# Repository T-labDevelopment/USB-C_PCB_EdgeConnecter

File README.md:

# USB-C PCBエッジ検証基板 Rev.0.7 — Windows短パス配布版

## 最新の修正（2026-11-13）
- **B.Cu接点24個から短い0.20mmの銅箔引出し配線を追加済み。** B1GND・B12GNDを含む。
- **LED帰路の`BAT_NEG`専用B.Cuベタを追加。** USB-CのGND検査端子には直接接続しない。
- GND検査は8経路（16接点）で、既存の対応する抵抗・LEDを維持。
- KiCadで銅箔ゾーンを再フィル（Bキー）してからDRCを実施する必要があります。**追加したゾーンの充填とERC/DRCは未検証です。**
- **未完成**：B.Cuの24本は引出し部分のみで、その他の全信号経路とBAT_POS給電配線は未配線です。製造承認済みではありません。

変更詳細：[GND・B.Cu接点引出し監査](REV07_BCU_GND_ESCAPE_FIX_2026-11-13.md)／[GND対応表](gnd_sense_map_rev07.csv)。

## Windows ZIP展開エラーへの対処

この`pkg-r07`は現行KiCadソースを最上位フォルダに格納し、不要な旧CH25電池ホルダーフットプリントと過去のZIPを除外した短パス配布専用ブランチです。

1. [pkg-r07 ZIP](https://github.com/T-labDevelopment/USB-C_PCB_EdgeConnecter/archive/refs/heads/pkg-r07.zip)をダウンロード。
2. `C:\PCB\`など短い場所に展開する。
3. 展開フォルダ直下の`USB_C_Loop_Tester.kicad_pro`をKiCad 10.x安定版で開く。
4. `USB_C_PCB_Edge.pretty/`・`USB_C_PCB_Edge.kicad_sym`・`fp-lib-table`・`sym-lib-table`はファイル階層を維持する。参照は`${KIPRJMOD}`相対パスです。

## 電気・機構構成

- J1/J2は14P USB2形状、J3/J4は実験用10P USB-Cエッジ接点形状。
- D1～D24の24個のLEDとR1～R24の22kΩ抵抗による個別接点導通表示。
- USB-Cの接点48パッドを基板内側へ2.4mm延長した形状を維持し、**その内側からB.Cu銅箔配線をさらに引出し**。
- ラッチKeepoutは16箇所、電池帰路B.Cuゾーンは1箇所。
- 電源は外付けCR2032×1、基板にはKiCad標準の2線はんだ付けパッド。
- 公称板厚0.8mm・2層・ENIG検討中。

**USB-CのGND接点を電池マイナスの銅箔面へ直接つなぐとLED検査を迂回するので禁止です。** ケーブルプラグ内部でGND・VBUSが共通化されるため、各LEDは接点1本ごとの良否を保証できません。

**残る必須事項**：すべての配線完成、KiCad 10 ERC/DRC、基板エッジ製造公差・マスク・機械嵌合・LED光量の実機確認。

Git管理の本開発作業ブランチ：`fix/usb-c-rev07-bcu-gnd-escape`。旧開発履歴は元リポジトリに維持し、`main`へは未統合。

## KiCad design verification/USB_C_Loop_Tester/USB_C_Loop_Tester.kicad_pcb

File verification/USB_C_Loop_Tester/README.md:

# USB-C 14P・10P 個別接点LED検証基板（Rev.0.7）

## 2026-11-13 B.Cu配線開始・GNDの帰路整理（最新作業版）

- J1～J4の下側接点全24個に、幅0.20mm・局所X=-0.20→+2.54mmの**同一ネットへの短いB.Cu配線**を配置しました。B1GND/B12GNDも含みます。
- USB-CのGND接点は導通試験用の独立ネットのまま残し、電池マイナスへ直結しません。
- LED24個のカソードと電池マイナスをつなぐ**BAT_NEG専用のB.Cuベタ（銅箔ゾーン）**を追加しました。USB側GND接点のネットとは別です。
- KiCadの **B（ゾーン再フィル）→DRC** で実際のクリアランス・給電帰路を必ず確認してください。B.Cu24本は接点からの引出し部分のみで、その他の信号とBAT_POSは未配線です。
- [GND8経路の対応表](gnd_sense_map_rev07.csv)／[GND・B.Cu変更監査](REV07_BCU_GND_ESCAPE_FIX_2026-11-13.md)。

**これまでの「PCBトラック0本」という説明は旧版の履歴です。最新作業版はトラック24本・銅箔ゾーン計17件です。ERC/DRC未実施・未完成のため製造承認不可。**

---

> **Windows ZIP展開エラー0x80010135への対応**：GitHubの長いブランチZIPではなく、現行KiCadファイルだけをルート階層に置いた短パス配布ブランチ [pkg-r07](https://github.com/T-labDevelopment/USB-C_PCB_EdgeConnecter/archive/refs/heads/pkg-r07.zip) を使用してください。旧CH25電池ホルダー用フットプリントは現行回路で未使用のため除外済みです。ダウンロード後は `C:\PCB\` など短い場所へ展開してください。元の開発データと履歴はこのブランチに保存しています。

## 2026-11-13 接点延長の反映（現行作業版）

画像で示された外側GND接点の引出し配線を短くするため、J1～J4の**全48銅パッドを基板内側へ2.4mm延長**しました。フットプリント内の外側嵌合端は維持し、内側端のみ `X=-2.385mm → +0.015mm` へ変更しています。配線開始位置はKeepout境界（X=-0.635mm）より基板内側へ0.65mm進みます。

- 14P/10PライブラリとPCB埋め込みの4コネクタ、`pad_positions.csv`を更新。
- 接点幅0.25mm、隣接銅間隔0.25mm、ラッチKeepout、端子ごとの独立ネットとLED・抵抗は維持。
- 露出銅箔とレジスト開口も延長するため、嵌合・半田レジスト・ENIGは未実機確認。
- **PCB配線は未実施**。KiCad 10のERC/DRC・製造検証は未実施。

詳細：[接点延長と静的検査](REV07_INBOARD_PAD_EXTENSION_2026-11-13.md)。

---

## 現行Rev.0.7 — 全24接点に独立した抵抗とLED

14PのJ1/J2に14系統（R1～R14、D1～D14）、10PのJ3/J4に10系統（R15～R24、D15～D24）を設けました。各USB-C銅接点はすべて別ネットで、グローバルラベルを介して専用抵抗・LEDへ接続します。

- 基板側の電源ネットのみBAT_POS/BAT_NEGを共用し、24個の抵抗入力／24個のLED帰路をまとめます。USB接点を基板上で短絡・グループ化しません。
- 電池は外付けCR2032×1、BT1は標準2線はんだ付けパッド。パッド1＋＝(31.0,18.0)mm、パッド2−＝(35.2,18.0)mm。
- **PCB：53フットプリント／146パッド／50ネット、銅箔配線0本。回路図：53部品・24分岐。**
- 0.8mm・2層・ENIG、USB-C接点形状とラッチKeepoutは旧版から維持。
- [全24回路の配線対応](channel_map_rev07.csv)／[回路と制約の説明](REV07_INDIVIDUAL_CONTACT_CIRCUIT.md)／[部品表](bom.csv)。

**重要：** USB-CのVBUS/GNDは通常ケーブル内部で共通化され、USB2.0ケーブルのB6/B7やCCは通常の1対1導通を前提にできません。すべてのLEDの点灯が正常なわけではなく、各接点1個だけの接触不良を保証して検出することもできません。

**未完了：** KiCad 10でのERC・DRC、PCB配線、Gerber、製造メーカーの加工承認、実機導通とLED光量試験。製造可能とは判定していません。

---

## 以下はRev.0.6以前の履歴であり、現行の回路仕様ではありません。

# USB-C 14P・10P 統合信号別LED導通検証基板（Rev.0.6）

## Rev.0.6 電源部の仕様変更：外付けCR2032／標準2線パッド

**採用仕様：基板直付けCH25-2032LFを廃止し、外部のCR2032ホルダーから絶縁リード線2本で給電する方式。**

以前のCH25-2032LF専用フットプリントは登録・極性確認・機構寸法の制約が多いため、現行PCBのBT1にはKiCad公式の標準フットプリント `Connector_Wire:SolderWire-0.25sqmm_1x02_P4.2mm_D0.65mm_OD1.7mm` を設定しました。独自の電池ホルダー用フットプリントを導入せずにKiCad 10の標準ライブラリで編集可能です。

- BT1パッド1（＋／BAT_POS）：基板座標(76.0, 90.0)mm、BT1パッド2（−／BAT_NEG）：(80.2, 90.0)mm。
- 2端子ピッチ4.2mm、ドリルφ0.85mm、ランドφ1.85mm。約0.25mm²の被覆付きリードを想定。
- CH25-2032LF（秋月電子100706）は**外付けでリード線を取り付ける場合の候補**として保持します。主基板へ直接実装しません。既に購入している場合も利用できますが、THT端子を配線用に使う加工・固定は実装時に確認してください。
- 電源はCR2032×1、スイッチなし。14P・10P各2端子／6個の信号別LEDは一切変更しません。
- 電池を入れない状態で極性と短絡を点検し、配線の引張り荷重がはんだ付け部分に掛からないよう固定・絶縁してください。
- **PCB銅箔配線は依然0本、KiCad 10のERC/DRCと実物検証は未実施です。**

詳しくは [新しいBT1外付け給電仕様](docs/BT1_EXTERNAL_CR2032.md) を参照してください。

## 旧検討案：BT1 CH25-2032LF基板直付け（Rev.0.5時点、現在は非採用）

> この節から下の旧Rev.0.5設計履歴は現在の採用仕様ではありません。Rev.0.6では外付けCR2032＋標準2線パッドが正式な接続方式です。

秋月電子 [販売コード100706](https://akizukidenshi.com/catalog/g/g100706/) のCR2032基板取付ホルダー `CH25-2032LF` に変更しました。旧Keystone用フットプリントは使用しません。新規`USB_C_Test_Parts.pretty`内の正規寸法図ベースの専用フットプリントに変更し、PCB側に電気端子用穴2個（20.0mmピッチ）、位置決めNPTH穴3個を追加しました。

**極性とPCB表裏方向はまだ実物確認前です。** 現在は下側リードをBAT_POS、上側をBAT_NEGとして仮定しています。設計確定前に電池を抜いた状態で金属クリップと2端子の導通を実測してください。詳細：[BT1 CH25-2032LF実装資料](docs/BT1_CH25-2032LF.md)。

PCBは依然として銅箔配線がありません。KiCad 10によるERC/DRC、実装、機械的嵌合は未検証です。

**以下は旧Rev.0.5時点の設計説明です。** ユーザー提示の左右2端子・中央電池・信号別LEDという概念図に基づき、14Pと10Pを1枚に統合し、ケーブルを挿入するだけで各信号の導通状態がLEDで見えるように再構成しました。

| 項目 | 14P検証（上段） | 10P検証（下段） |
| --- | --- | --- |
| USB-C接点 | J1（送出）、J2（受け） | J3（送出）、J4（受け） |
| VBUS | R1→D1 | R5→D5 |
| CC1/CC2（共用） | R2→D2 | R6→D6 |
| USB D+（A6/B6） | R3→D3 | 非搭載 |
| USB D−（A7/B7） | R4→D4 | 非搭載 |
| GND | J1→ケーブル→J2の共通帰路 | J3→ケーブル→J4の共通帰路 |

電源はBT1のCR2032（公称3V）1個。各LEDには22kΩを直列に接続し、入力スイッチ、制御IC、USB PD回路を置きません。

**実際の導通経路（14PのVBUS例）**

`CR2032＋ → R1 → J1 VBUS → 外部C-Cケーブル → J2 VBUS → D1（A→K） → J2 GND → 外部C-Cケーブル → J1 GND → CR2032−`

10PのVBUS/CC、および14PのCC/D+/D−も同様に、それぞれの抵抗とLEDを通ります。GNDは戻り線です。**J1とJ2、J3とJ4を基板上で直接配線しない**ので、未接続のケーブルは導通扱いになりません。電池の＋と−の不要な交差は避けてあります。

### この版で実施したこと

- 回路図は17部品、**全74端子**、**85本のワイヤー／18か所のジャンクション／16ネット／ネットラベル0**。端子と配線は50mil（1.27mm）グリッドに配置。
- 回路図内の意図しない異ネット接続0、途中で分断されたネット0、配線されていない端子0を静的検査。
- 各LEDの極性を確認。モデル上で「未接続・14Pのみ・10Pのみ・双方・1信号断線・GND断線」計8パターンの期待点灯を確認。
- PCBは既存のUSB-Cエッジ接点・電池ホルダーを維持し、LED D1～D6と抵抗R5/R6の配置を整理。PCB74パッドの番号・ネット割当は変更しません。

**重要：これは電気的な論理構成が成立することの検証です。** KiCad 10でのERC実行・DRC・実機嵌合・LED光量試験を実施したという意味ではありません。PCBの銅箔配線は依然0本で、製造しても動作しません。

詳細は [Rev.0.5統合回路・論理検証資料](REV05_UNIFIED_CIRCUIT.md) を参照してください。旧Rev.0.4以前の記載は以下に履歴として保持します。

---

## 過去の検討・修正履歴

## ERC実測レポートに基づく修正（2026-11-12 / Rev.0.4）

ユーザー提供のKiCad ERCレポート：**20エラー（未接続ピン18、電源入力未駆動2）、19警告（未接続配線端19ではなく18、シンボル不一致1）**。

- 単なる文字ベースの端点一致ではKiCad ERCで多数の未接続が残ったため、電源配線・LED帰路を端子直結の連続線に再配置し直しました。
- 14P/10P各2個の全接点、6灯LED、CR2032、6個の22kΩは維持。ネットラベルは0個、**実配線63本・明示接続点18個**。
- USB-C検証治具ではVBUS/GNDは電源入力ではなく測定用受動接点です。製品用の元シンボルは変更せず、`USB_C_Test_14P_USB2_NoShield` と `USB_C_Test_10P_Power_NoShield` をプロジェクト専用に追加し、各端子のVBUS/GNDを受動型として設定。**PWR_FLAGは設置せず**、電源の存在を偽装しない方針です。
- `Device:Battery_Cell` キャッシュをKiCad 10.x系の正式シンボルデータに更新しました。お使いのローカルKiCadライブラリと同一リビジョンであるかは未確認です。
- **静的監査：74シンボル端子／74PCBパッド、16ネットに一致、未接続端点0件、PCBネットとの相違0件。** 交差のみの2箇所はジャンクションなしで別ネット扱いです。
- **重要：修正版のKiCad 10 ERCはまだ実行していません。エラー・警告が0件になったとは断定できません。** 結果確認には再度KiCadのERCが必要です。
- PCBは配置案のままで、**銅箔配線は0本**（製造不可）。端子形状・基板厚は変更していません。

詳細：[ERC修正監査](ERC_REPAIR_AUDIT_2026-11-12.md)。

## Rev.0.3（2026-11-12）回路図の実配線化・部品再配置

- 回路図のネットラベルを**全廃（0個）**し、94本のワイヤーと18個の接続点で全信号を直接接続しました。配線・接続点は50milグリッドに整列しています。
- J1/J2（14P）は回路図上段、J3/J4（10P）は下段。送出側へR1～R6、受け側へD1～D6を配置し、CR2032の共通給電と、ケーブル経由のGND帰路を明示しました。
- PCBではUSB-Cエッジ端子と電池ホルダーの位置を固定し、抵抗6個・LED6個を検査系統ごとに再配置。パッド座標一覧も更新しました。
- 静的な接続グラフ検査：**74端子／16ネット、未接続端子0、異ネット短絡0**。基板上の配線は**0本**で未完成です。
- 回路図をKiCad 10で実際に開いて確認する工程、ERC/DRC、製造可否とLED点灯試験は**未実施**です。

**採用案：ケーブルを挿すだけで該当するLEDが点灯。スイッチは設けません。**

- 1枚の基板に14Pエッジ端子×2（J1/J2）、10Pエッジ端子×2（J3/J4）。
- CR2032×1、3mm高輝度・低電流赤色LED×6、22kΩ×6（いずれも手はんだしやすいTHT）。
- 14P/10Pそれぞれにe-marker非搭載・無通電の受動型USB-C⇔USB-Cケーブルを接続して判定。
- FR-4、2層、板厚0.8mm、接点ENIG、暫定突出長6.2mm。USB接点部分にシルクなし。

## KiCad 10での開き方

1. 現行Rev.0.6はGitHubの `feature/usb-c-external-cr2032-wire-pads` ブランチから取得します。`verification/USB_C_Loop_Tester/` 以下のファイルとライブラリをフォルダーごと保持してください。`verification/releases/` にある旧版ZIPはRev.0.6以前の履歴データです。
2. `verification/USB_C_Loop_Tester/USB_C_Loop_Tester.kicad_pro` をダブルクリックするか、KiCad 10の「ファイル → プロジェクトを開く」から選択します。
3. 左のプロジェクトツリーで同名の `.kicad_sch`（回路図）と `.kicad_pcb`（基板）を選択します。
4. `USB_C_PCB_Edge.kicad_sym`、`USB_C_PCB_Edge.pretty/`、`sym-lib-table`、`fp-lib-table` はプロジェクトに同梱されています。**フォルダー構成を変更しないでください**。標準のDevice/LED、Device/R、Device/Battery_Cell等のKiCad 10標準ライブラリは本体側が必要です。

**重要**：今回はKiCadが認識するプロジェクト構成とファイル構文を静的検査したものです。この環境ではKiCad 10の実行ファイルがなく、実際のGUI読み込みとERC/DRCには未着手です。またPCBは配線0本で、製造しても動作しません。

## LEDと信号の対応

| 系統 | LED | 確認する信号 | 同一機能として集約するパッド |
|---|---|---|---|
| 14P（J1⇄J2） | D1 | VBUS | A4/A9/B4/B9 |
| 14P（J1⇄J2） | D2 | CC | A5(CC1)/B5(CC2) |
| 14P（J1⇄J2） | D3 | D+ | A6/B6 |
| 14P（J1⇄J2） | D4 | D− | A7/B7 |
| 10P（J3⇄J4） | D5 | VBUS | A4/A9/B4/B9 |
| 10P（J3⇄J4） | D6 | CC | A5(CC1)/B5(CC2) |

GND（A1/A12/B1/B12）は14Pと10Pで独立した**共通の帰路**として使います。基板内で戻り側GND（J2/J4）をBAT_NEGに直結していないため、ケーブルのGND経路が断線した場合は、その系統のLEDがまとめて消灯します。GNDだけの独立LEDは設けません。

**同じ機能の端子はLEDを共用**しますが、14Pと10Pでは検証対象が違うため、同じVBUSやCCであっても系統間でLEDを共用しません。片方のケーブルだけが接続されたときにもう一方の表示が点灯しないようにするためです。

### 回路経路（各LED共通）

`CR2032+ → R1～R6(各22k) → J1/J3側の該当信号 → C-Cケーブル → J2/J4側の該当信号 → D1～D6（アノード→カソード） → 戻り側GND → C-CケーブルのGND → CR2032−`

接続した信号と共通GNDの両方に導通があれば、対応するLEDだけが点灯します。抜けば消灯します。2本同時接続時には最大6灯が点灯します。

## 判定上の制限

- **e-marker付きのパッシブケーブルは検証対象から除外します。** この簡易治具はCC1/CC2を直結しているため、ケーブルのVCONN側Ra（約1kΩ）に影響され、正常なケーブルでもCC LEDが点灯しない可能性があります。e-marker非搭載の一般的なUSB 2.0 C-Cケーブルを基準に評価してください。

- 表裏のA/B端子や複数VBUS・GND端子を並列接続しているため、**同一信号群内の個別パッド1個の断線は判別できない場合があります**。
- CCは一般のC-Cケーブルで1本の有効信号線です。A5/B5の両方をこの**無電源ケーブル検証専用基板**では意図的にまとめています。実製品のUSB-CデバイスではCC1とCC2を直結せず、規格どおりの終端を使用してください。
- LED点灯は簡易導通確認であり、接触抵抗の定量評価、隣接信号短絡の網羅的検出、USB2.0列挙、USB PD、ESP32の書き込み成功を保証しません。
- ケーブルの**両端をそれぞれ反転**して、点灯の変化と接触安定性を確認してください。

## 電源・安全

22kΩで赤色LED順方向電圧を約1.8Vと仮定すると、1灯あたり約0.055mA、6灯で合計約0.33mAです（**計算上の参考値で実測ではありません**）。CR2032の標準連続負荷0.2mAより大きいため、挿入試験は短時間とし、使用後はケーブルを抜いて消灯させてください。低電流でも見える赤色LEDの部品選定・光量は実機確認対象です。

**この基板は外部のUSB機器に接続できません。** CR2032による電圧をUSB端子に出す検証治具です。PC、充電器、モバイルバッテリー、給電中のUSB機器、アクティブケーブル等に接続しないでください。無通電の受動型C-Cケーブルのみを試験対象とします。

## 製造・動作検証状態

- KiCad回路図、PCB内の部品配置とパッドのネット割当、BOMを更新しました。
- PCBは**配線未実施（銅箔配線セグメント0件）**です。このデータをそのまま製造してもLEDは動作しません。
- KiCad 10実環境のERC/DRC、外形の接続、製造データ、嵌合・導通・光量確認は未実施。
- GND接点とEdge.Cutsとの約0.17mmクリアランスについて、基板メーカーの加工承認が必要です。
- 旧来の2灯直列方式は `../USB_C_Loop_Tester_Series/`、スイッチ付き案はGit履歴で参照できます。

## 参考
- USB Type-C規格資料：https://www.usb.org/documents
- Panasonic CR2032（3V、標準負荷0.2mA）：https://energy.panasonic.com/jp/business/products/lithium/coin-cr-standard/models/CR2032
- PCBエッジ方式先行例：https://github.com/AnasMalas/pcb-edge-usb-c

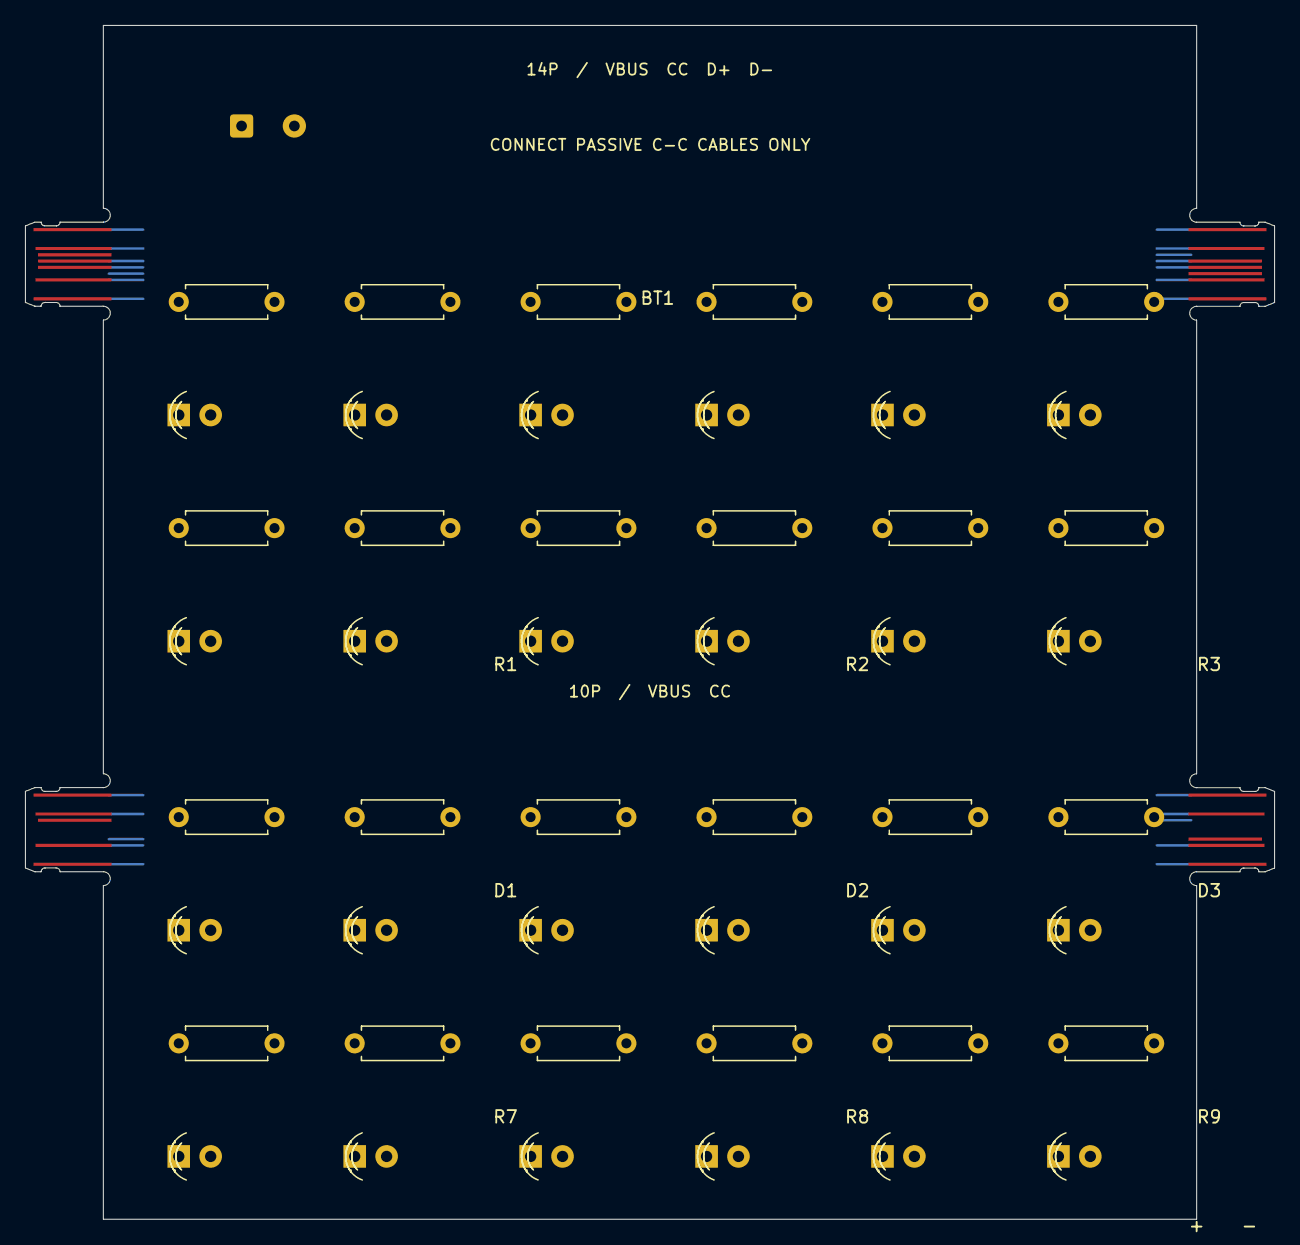
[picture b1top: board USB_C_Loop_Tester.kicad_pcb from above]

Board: 2 copper layers, 99.4 x 95.0 mm, 53 parts (0 on the bottom side), 50 nets.

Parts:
BT1: CR2032_EXTERNAL; SolderWire-0.25sqmm_1x02_P4.2mm_D0.65mm_OD1.7mm
D1, D2, D3, D4, D5, D6, D7, D8, D9, D10, D11, D12, D13, D14, D15, D16, D17, D18, D19, D20, D21, D22, D23, D24: RED; LED_D3.0mm
J1, J2: 14P; USB_C_Edge_14P_USB2_NoSilk
J3, J4: 10P; USB_C_Edge_10P_Power_NoSilk
R1, R2, R3, R4, R5, R6, R7, R8, R9, R10, R11, R12, R13, R14, R15, R16, R17, R18, R19, R20, R21, R22, R23, R24: 22k; R_Axial_DIN0207_L6.3mm_D2.5mm_P7.62mm_Horizontal

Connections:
BAT_NEG: BT1.2, D1.1, D2.1, D3.1, D4.1, D5.1, D6.1, D7.1, D8.1, D9.1, D10.1, D11.1, D12.1, D13.1, D14.1, D15.1, D16.1, D17.1, D18.1, D19.1, D20.1, D21.1, D22.1, D23.1, D24.1
BAT_POS: BT1.1, R1.1, R2.1, R3.1, R4.1, R5.1, R6.1, R7.1, R8.1, R9.1, R10.1, R11.1, R12.1, R13.1, R14.1, R15.1, R16.1, R17.1, R18.1, R19.1, R20.1, R21.1, R22.1, R23.1, R24.1
DST_J2_A1GND: D1.2, J2.A1GND
DST_J2_A4VBUS: D2.2, J2.A4VBUS
DST_J2_A5CC1: D3.2, J2.A5CC1
DST_J2_A6D+: D4.2, J2.A6D+
DST_J2_A7D-: D5.2, J2.A7D-
DST_J2_A9VBUS: D6.2, J2.A9VBUS
DST_J2_A12GND: D7.2, J2.A12GND
DST_J2_B1GND: D8.2, J2.B1GND
DST_J2_B4VBUS: D9.2, J2.B4VBUS
DST_J2_B5CC2: D10.2, J2.B5CC2
DST_J2_B6D+: D11.2, J2.B6D+
DST_J2_B7D-: D12.2, J2.B7D-
DST_J2_B9VBUS: D13.2, J2.B9VBUS
DST_J2_B12GND: D14.2, J2.B12GND
DST_J4_A1GND: D15.2, J4.A1GND
DST_J4_A4VBUS: D16.2, J4.A4VBUS
DST_J4_A5CC1: D17.2, J4.A5CC1
DST_J4_A9VBUS: D18.2, J4.A9VBUS
DST_J4_A12GND: D19.2, J4.A12GND
DST_J4_B1GND: D20.2, J4.B1GND
DST_J4_B4VBUS: D21.2, J4.B4VBUS
DST_J4_B5CC2: D22.2, J4.B5CC2
DST_J4_B9VBUS: D23.2, J4.B9VBUS
DST_J4_B12GND: D24.2, J4.B12GND
SRC_J1_A1GND: J1.A1GND, R1.2
SRC_J1_A4VBUS: J1.A4VBUS, R2.2
SRC_J1_A5CC1: J1.A5CC1, R3.2
SRC_J1_A6D+: J1.A6D+, R4.2
SRC_J1_A7D-: J1.A7D-, R5.2
SRC_J1_A9VBUS: J1.A9VBUS, R6.2
SRC_J1_A12GND: J1.A12GND, R7.2
SRC_J1_B1GND: J1.B1GND, R8.2
SRC_J1_B4VBUS: J1.B4VBUS, R9.2
SRC_J1_B5CC2: J1.B5CC2, R10.2
SRC_J1_B6D+: J1.B6D+, R11.2
SRC_J1_B7D-: J1.B7D-, R12.2
SRC_J1_B9VBUS: J1.B9VBUS, R13.2
SRC_J1_B12GND: J1.B12GND, R14.2
SRC_J3_A1GND: J3.A1GND, R15.2
SRC_J3_A4VBUS: J3.A4VBUS, R16.2
SRC_J3_A5CC1: J3.A5CC1, R17.2
SRC_J3_A9VBUS: J3.A9VBUS, R18.2
SRC_J3_A12GND: J3.A12GND, R19.2
SRC_J3_B1GND: J3.B1GND, R20.2
SRC_J3_B4VBUS: J3.B4VBUS, R21.2
SRC_J3_B5CC2: J3.B5CC2, R22.2
SRC_J3_B9VBUS: J3.B9VBUS, R23.2
SRC_J3_B12GND: J3.B12GND, R24.2

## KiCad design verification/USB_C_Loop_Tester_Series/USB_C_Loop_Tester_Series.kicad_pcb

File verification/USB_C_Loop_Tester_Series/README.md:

> **旧案（優先採用対象外）**：この2灯直列ループ版は比較・履歴用です。現在の試作案は [6灯・信号別LED基板](../USB_C_Loop_Tester/README.md) です。USBケーブル挿入だけで点灯し、ボタンはありません。

# USB-C PCB Edge CR2032 Cable-Insert LED Tester

**Cable connection itself is the ON switch.** No pushbuttons or other operating switches.

- **One board**: USB-C PCB-edge 14P ×2 (J1/J2), 10P ×2 (J3/J4); two independent USB-C to USB-C **passive, unpowered** cable loops
- **Power**: CR2032 ×1 (BT1), shared by both loops
- **Indicators**: two low-current red LEDs (D1/D2), one for each connector pair
- **Current limit**: 2.2kΩ (R1/R2), one per LED loop
- **Board**: nominal FR-4 0.8mm, two layers, ENIG, 6.2mm protrusion, no silk around contact tongues

## What happens

| 14P cable (J1→J2) | 10P cable (J3→J4) | LEDs |
|---|---|---|
| Absent | Absent | Both off |
| Connected | Absent | D1 on, D2 off |
| Absent | Connected | D1 off, D2 on |
| Connected | Connected | Both on |

### Serial test paths

14P: CR2032+ → R1 → J1 VBUS → cable → J2 VBUS → CC → cable → J1 CC → D+ → cable → J2 D+ → D− → cable → J1 D− → GND → cable → J2 GND → D1 anode → cathode → CR2032−.

10P: CR2032+ → R2 → J3 VBUS → cable → J4 VBUS → CC → cable → J3 CC → GND → cable → J4 GND → D2 anode → cathode → CR2032−.

**LEDs light whenever the corresponding cable completes the loop and there is no open connection.** Disconnect the cable to switch off and save battery; leaving both connected causes continuous battery drain.

### Safety / limits

This board is a battery-powered electrical **test fixture**, NOT a USB host, device or USB-PD circuit. The connector CC1/CC2 pads are intentionally bridged. **Never connect to a computer, charger, power bank, USB-enabled board, or external power source, especially with CR2032 installed. Use passive C-to-C cables only.**

The LED tests only **grouped serial continuity**, not every redundant contact, actual USB2 enumeration, signal integrity, PD negotiation, shorts between unselected nets, or reliable firmware flashing. Flip each cable end separately and test both orientations; some active/e-marked cables may not support the fixture's CC test. Select low-current high-brightness red LEDs.

CR2032 standard continuous current is typically about 0.2mA (Panasonic); a 2.2kΩ series resistor and red LED can demand several tenths of a milliampere. Intermittent testing is recommended. No extra switch is installed by design.

### Build status

The KiCad schematic, BOM and **footprint placement** are updated. **The PCB traces remain unrouted (0 copper segments).** The CAD files have not passed native KiCad 10 ERC/DRC or physical validation, and the 0.17mm GND contact to Edge.Cuts issue remains. **Do not order as a functional PCB yet.**

The older 6-LED/6-button study remains under `../USB_C_Loop_Tester`; it is not the preferred prototype.

### References
- https://developerhelp.microchip.com/xwiki/bin/view/applications/usb/typec-features/cc-vconn-signals/
- https://energy.panasonic.com/jp/business/products/lithium/coin-cr-standard/models/CR2032
- https://github.com/AnasMalas/pcb-edge-usb-c

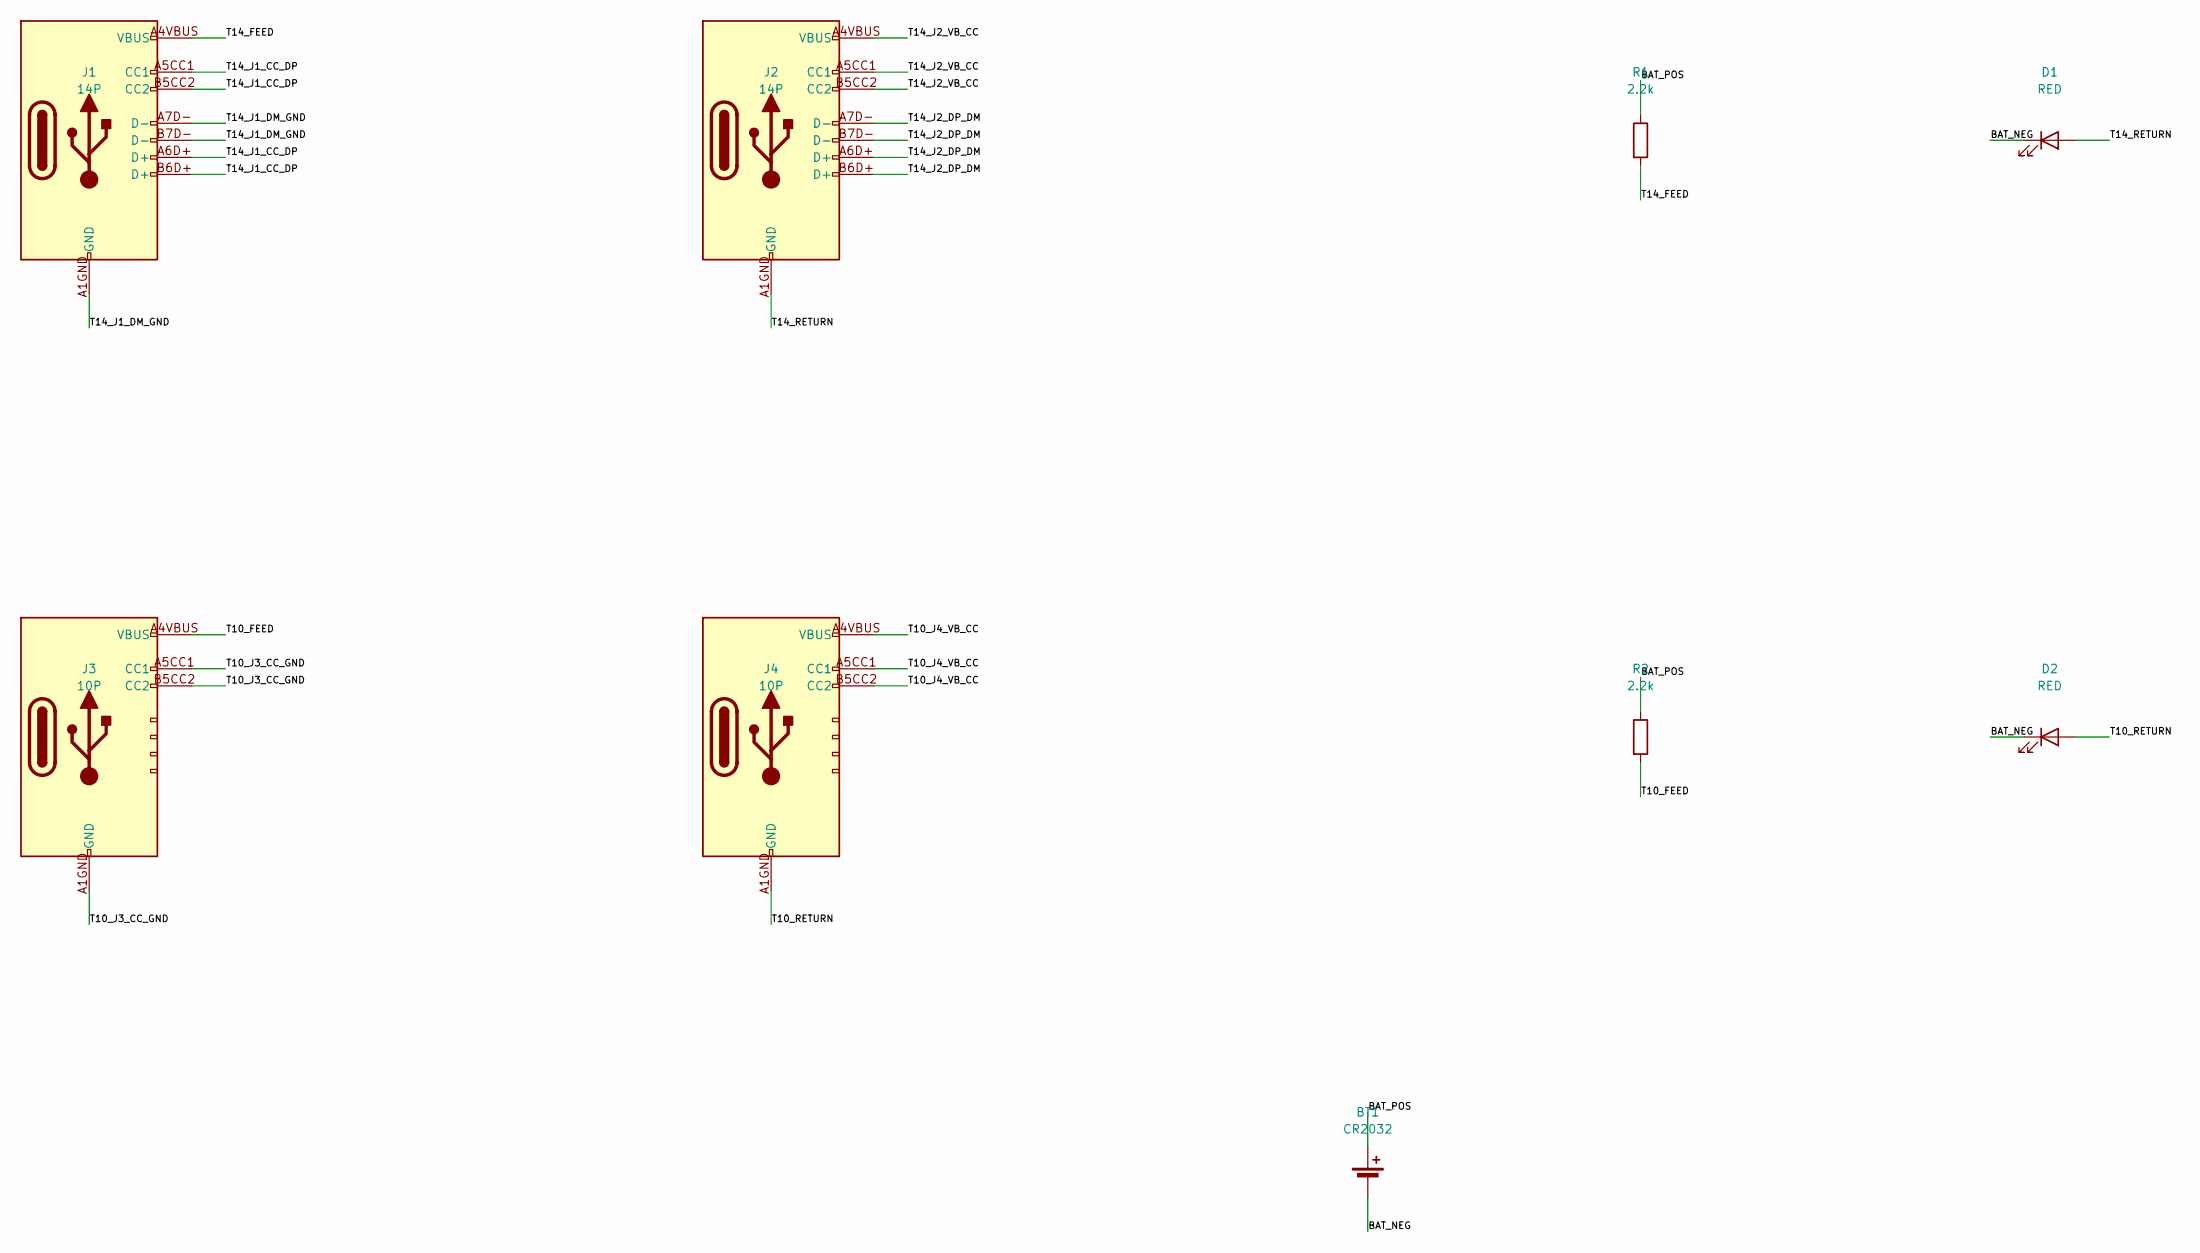
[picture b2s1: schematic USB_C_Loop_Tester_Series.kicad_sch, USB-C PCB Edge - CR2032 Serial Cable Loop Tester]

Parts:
BT1: CR2032; BatteryHolder_Keystone_103_1x20mm
D1, D2: RED; LED_D3.0mm
J1, J2: 14P; USB_C_Edge_14P_USB2_NoSilk
J3, J4: 10P; USB_C_Edge_10P_Power_NoSilk
R1, R2: 2.2k; R_Axial_DIN0207_L6.3mm_D2.5mm_P7.62mm_Horizontal

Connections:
BAT_NEG: BT1.2 (-), D1.1 (K), D2.1 (K)
BAT_POS: BT1.1 (+), R1.1, R2.1
T10_FEED: J3.A4VBUS (VBUS), J3.A9VBUS (VBUS), J3.B4VBUS (VBUS), J3.B9VBUS (VBUS), R2.2
T10_J3_CC_GND: J3.A1GND (GND), J3.A5CC1 (CC1), J3.A12GND (GND), J3.B1GND (GND), J3.B5CC2 (CC2), J3.B12GND (GND)
T10_J4_VB_CC: J4.A4VBUS (VBUS), J4.A5CC1 (CC1), J4.A9VBUS (VBUS), J4.B4VBUS (VBUS), J4.B5CC2 (CC2), J4.B9VBUS (VBUS)
T10_RETURN: D2.2 (A), J4.A1GND (GND), J4.A12GND (GND), J4.B1GND (GND), J4.B12GND (GND)
T14_FEED: J1.A4VBUS (VBUS), J1.A9VBUS (VBUS), J1.B4VBUS (VBUS), J1.B9VBUS (VBUS), R1.2
T14_J1_CC_DP: J1.A5CC1 (CC1), J1.A6D+ (D+), J1.B5CC2 (CC2), J1.B6D+ (D+)
T14_J1_DM_GND: J1.A1GND (GND), J1.A7D- (D-), J1.A12GND (GND), J1.B1GND (GND), J1.B7D- (D-), J1.B12GND (GND)
T14_J2_DP_DM: J2.A6D+ (D+), J2.A7D- (D-), J2.B6D+ (D+), J2.B7D- (D-)
T14_J2_VB_CC: J2.A4VBUS (VBUS), J2.A5CC1 (CC1), J2.A9VBUS (VBUS), J2.B4VBUS (VBUS), J2.B5CC2 (CC2), J2.B9VBUS (VBUS)
T14_RETURN: D1.2 (A), J2.A1GND (GND), J2.A12GND (GND), J2.B1GND (GND), J2.B12GND (GND)

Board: 2 copper layers, 9 parts (0 on the bottom side), 12 nets, no tracks yet.

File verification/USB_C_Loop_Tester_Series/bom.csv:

Reference,Quantity,Value,Footprint,Notes
J1 J2,2,PCB edge USB-C 14P,USB_C_PCB_Edge:USB_C_Edge_14P_USB2_NoSilk,Board integral contacts
J3 J4,2,PCB edge USB-C 10P,USB_C_PCB_Edge:USB_C_Edge_10P_Power_NoSilk,Simplified nonstandard Power-Only variant
BT1,1,CR2032 THT holder,Battery:BatteryHolder_Keystone_103_1x20mm,Actual holder compatibility to verify
R1 R2,2,2.2k 1/4W,Resistor_THT:R_Axial_DIN0207_L6.3mm_D2.5mm_P7.62mm_Horizontal,Limits indicator current
D1 D2,2,Low-current red 3mm LED,LED_THT:LED_D3.0mm,Pad 2 is anode
CR2032,1,3V coin cell,-,Remove cables between tests to prevent continuous consumption
